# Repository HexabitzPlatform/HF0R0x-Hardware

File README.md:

# HF0R0x-Hardware
Hexabitz Arduino Interface Hardware Design

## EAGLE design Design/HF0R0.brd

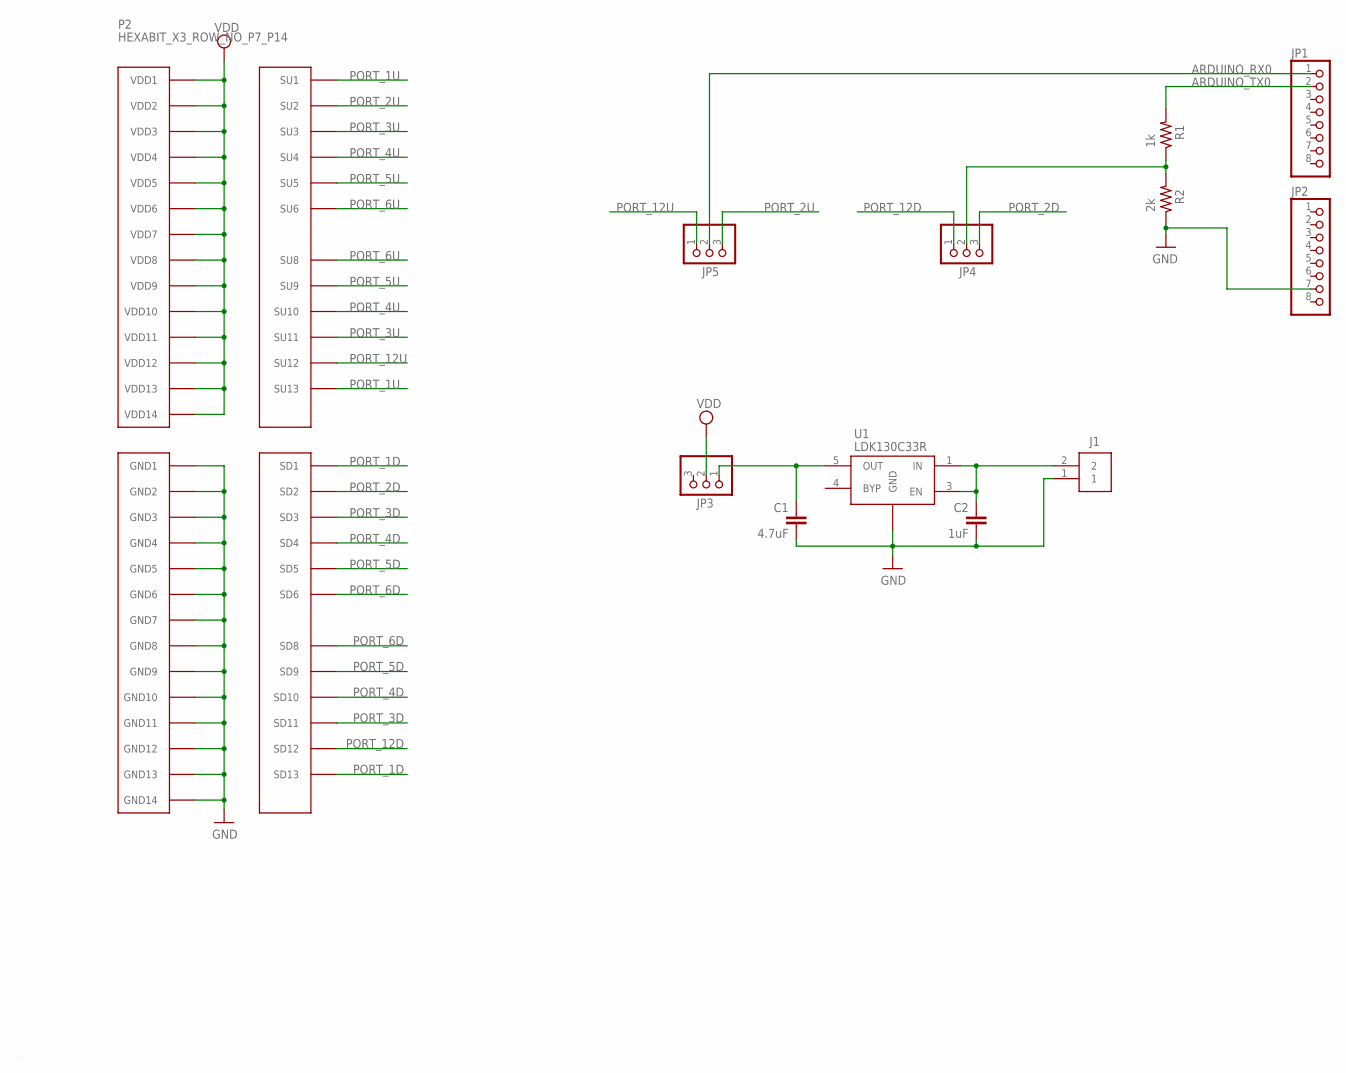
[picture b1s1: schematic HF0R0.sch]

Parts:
C1: 4.7uF; C-0805
C2: 1uF; C-0805
J1: 3-644456-2; TE_3-644456-2
JP1, JP2: PINHD-1X8; 1X08
JP3, JP4, JP5: PINHD-1X3; 1X03
P2: HEXABIT_X3_ROW_NO_P7_P14
R1: 1k; R-0603
R2: 2k; R-0603
U1: LDK130C33R; SOT65P210X110-5N
U$1: HEXABITZ-LOGO+SLOGAN

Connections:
ARDUINO_RX0: JP1.1, JP5.2
ARDUINO_TX0: JP1.2, R1.2
GND: C1.2, C2.2, J1.1, JP2.7, P2.PAD_PD15 (GND1), P2.PAD_PD16 (GND2), P2.PAD_PD17 (GND3), P2.PAD_PD18 (GND4), P2.PAD_PD19 (GND5), P2.PAD_PD20 (GND6), P2.PAD_PD21 (GND7), P2.PAD_PD22 (GND8), P2.PAD_PD23 (GND9), P2.PAD_PD24 (GND10), P2.PAD_PD25 (GND11), P2.PAD_PD26 (GND12), P2.PAD_PD27 (GND13), P2.PAD_PD28 (GND14), R2.1, U1.2 (GND)
unnamed: C1.1, JP3.1, U1.5 (OUT)
unnamed: JP4.2, R1.1, R2.2
unnamed: C2.1, J1.2, U1.1 (IN), U1.3 (EN)
PORT_1D: P2.PAD_PD1 (SD1), P2.PAD_PD13 (SD13)
PORT_1U: P2.PAD_PU1 (SU1), P2.PAD_PU13 (SU13)
PORT_2D: JP4.3, P2.PAD_PD2 (SD2)
PORT_2U: JP5.3, P2.PAD_PU2 (SU2)
PORT_3D: P2.PAD_PD3 (SD3), P2.PAD_PD11 (SD11)
PORT_3U: P2.PAD_PU3 (SU3), P2.PAD_PU11 (SU11)
PORT_4D: P2.PAD_PD4 (SD4), P2.PAD_PD10 (SD10)
PORT_4U: P2.PAD_PU4 (SU4), P2.PAD_PU10 (SU10)
PORT_5D: P2.PAD_PD5 (SD5), P2.PAD_PD9 (SD9)
PORT_5U: P2.PAD_PU5 (SU5), P2.PAD_PU9 (SU9)
PORT_6D: P2.PAD_PD6 (SD6), P2.PAD_PD8 (SD8)
PORT_6U: P2.PAD_PU6 (SU6), P2.PAD_PU8 (SU8)
PORT_12D: JP4.1, P2.PAD_PD12 (SD12)
PORT_12U: JP5.1, P2.PAD_PU12 (SU12)
VDD: JP3.2, P2.PAD_PU15 (VDD1), P2.PAD_PU16 (VDD2), P2.PAD_PU17 (VDD3), P2.PAD_PU18 (VDD4), P2.PAD_PU19 (VDD5), P2.PAD_PU20 (VDD6), P2.PAD_PU21 (VDD7), P2.PAD_PU22 (VDD8), P2.PAD_PU23 (VDD9), P2.PAD_PU24 (VDD10), P2.PAD_PU25 (VDD11), P2.PAD_PU26 (VDD12), P2.PAD_PU27 (VDD13), P2.PAD_PU28 (VDD14)

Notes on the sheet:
C:/Users/Moazzen/Pictures/Presentation1.bmp

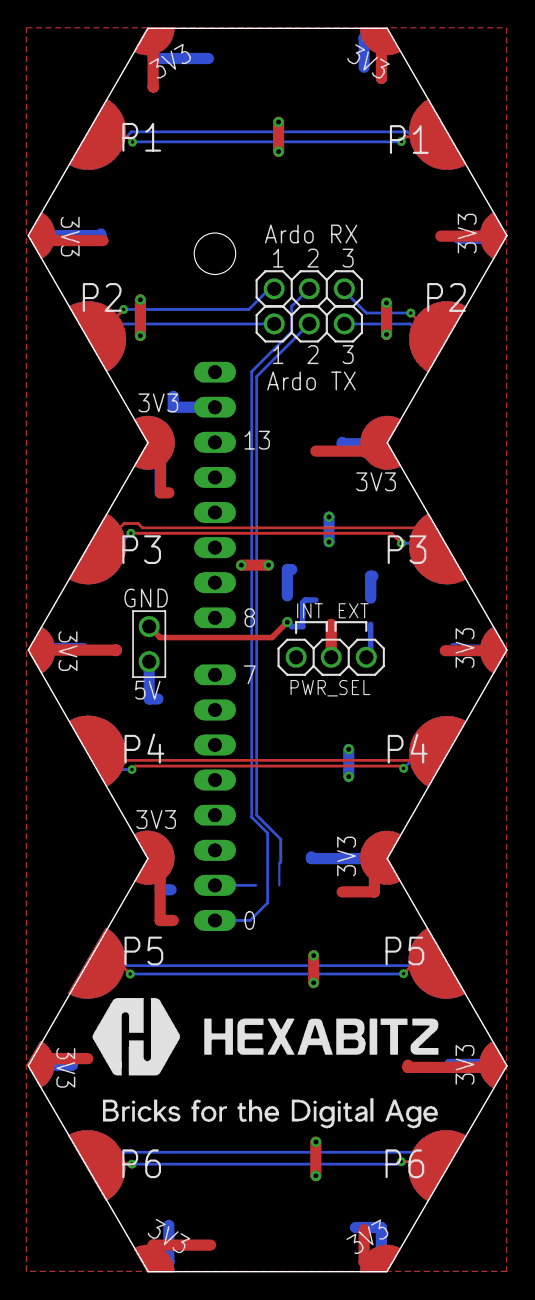
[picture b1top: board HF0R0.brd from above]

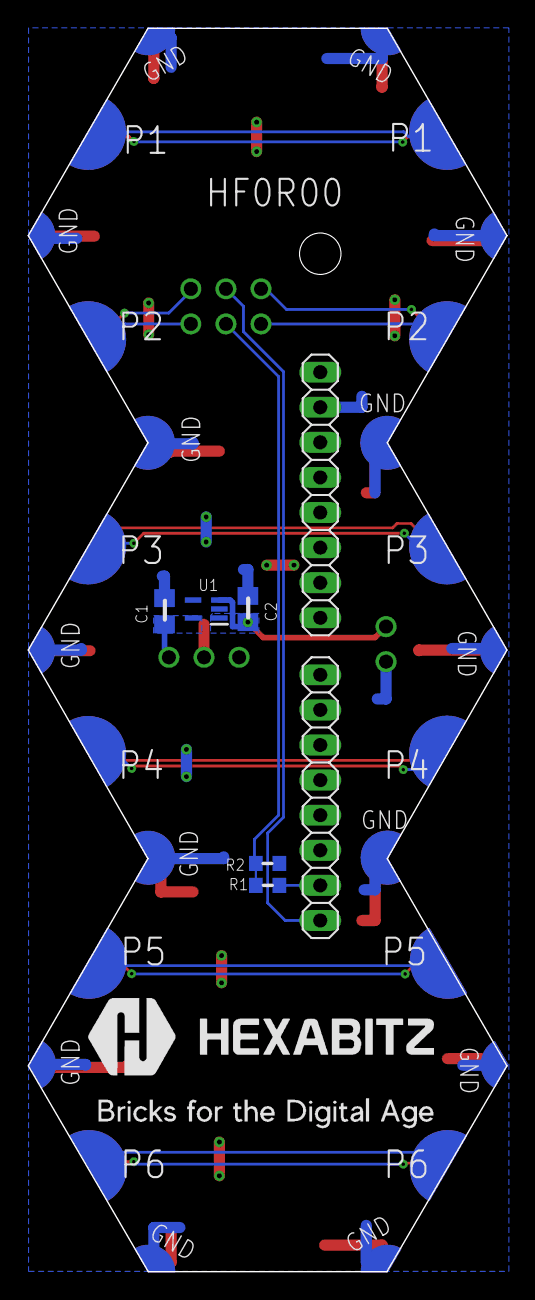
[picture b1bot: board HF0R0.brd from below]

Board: 2 copper layers, 34.6 x 90.0 mm, 13 parts (7 on the bottom side), 21 nets.

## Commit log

2024-12-18 -The final design, all done.
